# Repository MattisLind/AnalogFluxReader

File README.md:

# AnalogFluxReader
A daughter board to the cheap Cypress  FX2LP demo boards for reading floppy fluxes in analog domain.

This is still very much work in progress. The idea with this project is to read those problematic Memorex 651 disks that I so far has been unsuccessful in reading.

Instead of using the read detector in the drive the idea is to connect the differential signal from the head to this board and then do the all processing in the host PC. 

Please note that some component values, (R and C) in the analog path is just placeholders and is selected in a later stage. The idea that some of them should be easy to change so that filter cut-off frequency and gain can be changed.

The board sits on top of one of those small Cypress FX2LP boards that can be purchased from China cheaply. The FX2LP chip provide a programmable USB interface with high performance. Giving the possibility to sample the A/D converter with up to 48 MSMPS.

## Links
* [The Uncomplicated Universal Usb board](http://lea.hamradio.si/~s57uuu/uuusb/index.htm)
* [adhdengineering](https://adhdengineering.wordpress.com/tag/fx2lp/)
* [Electronics -- USB-FX2 Interface Board (USB-2.0)](https://www.triplespark.net/elec/periph/USB-FX2/)
* [EZ-USB on Linux](http://www.linux-usb.org/ezusb/)
* [Library routines for creating firmware for the Cypress FX2 (CY7C68013 and variants) with SDCC](https://github.com/djmuhlestein/fx2lib)
* [EZ-USB® Technical Reference Manual](https://www.cypress.com/file/126446/download)

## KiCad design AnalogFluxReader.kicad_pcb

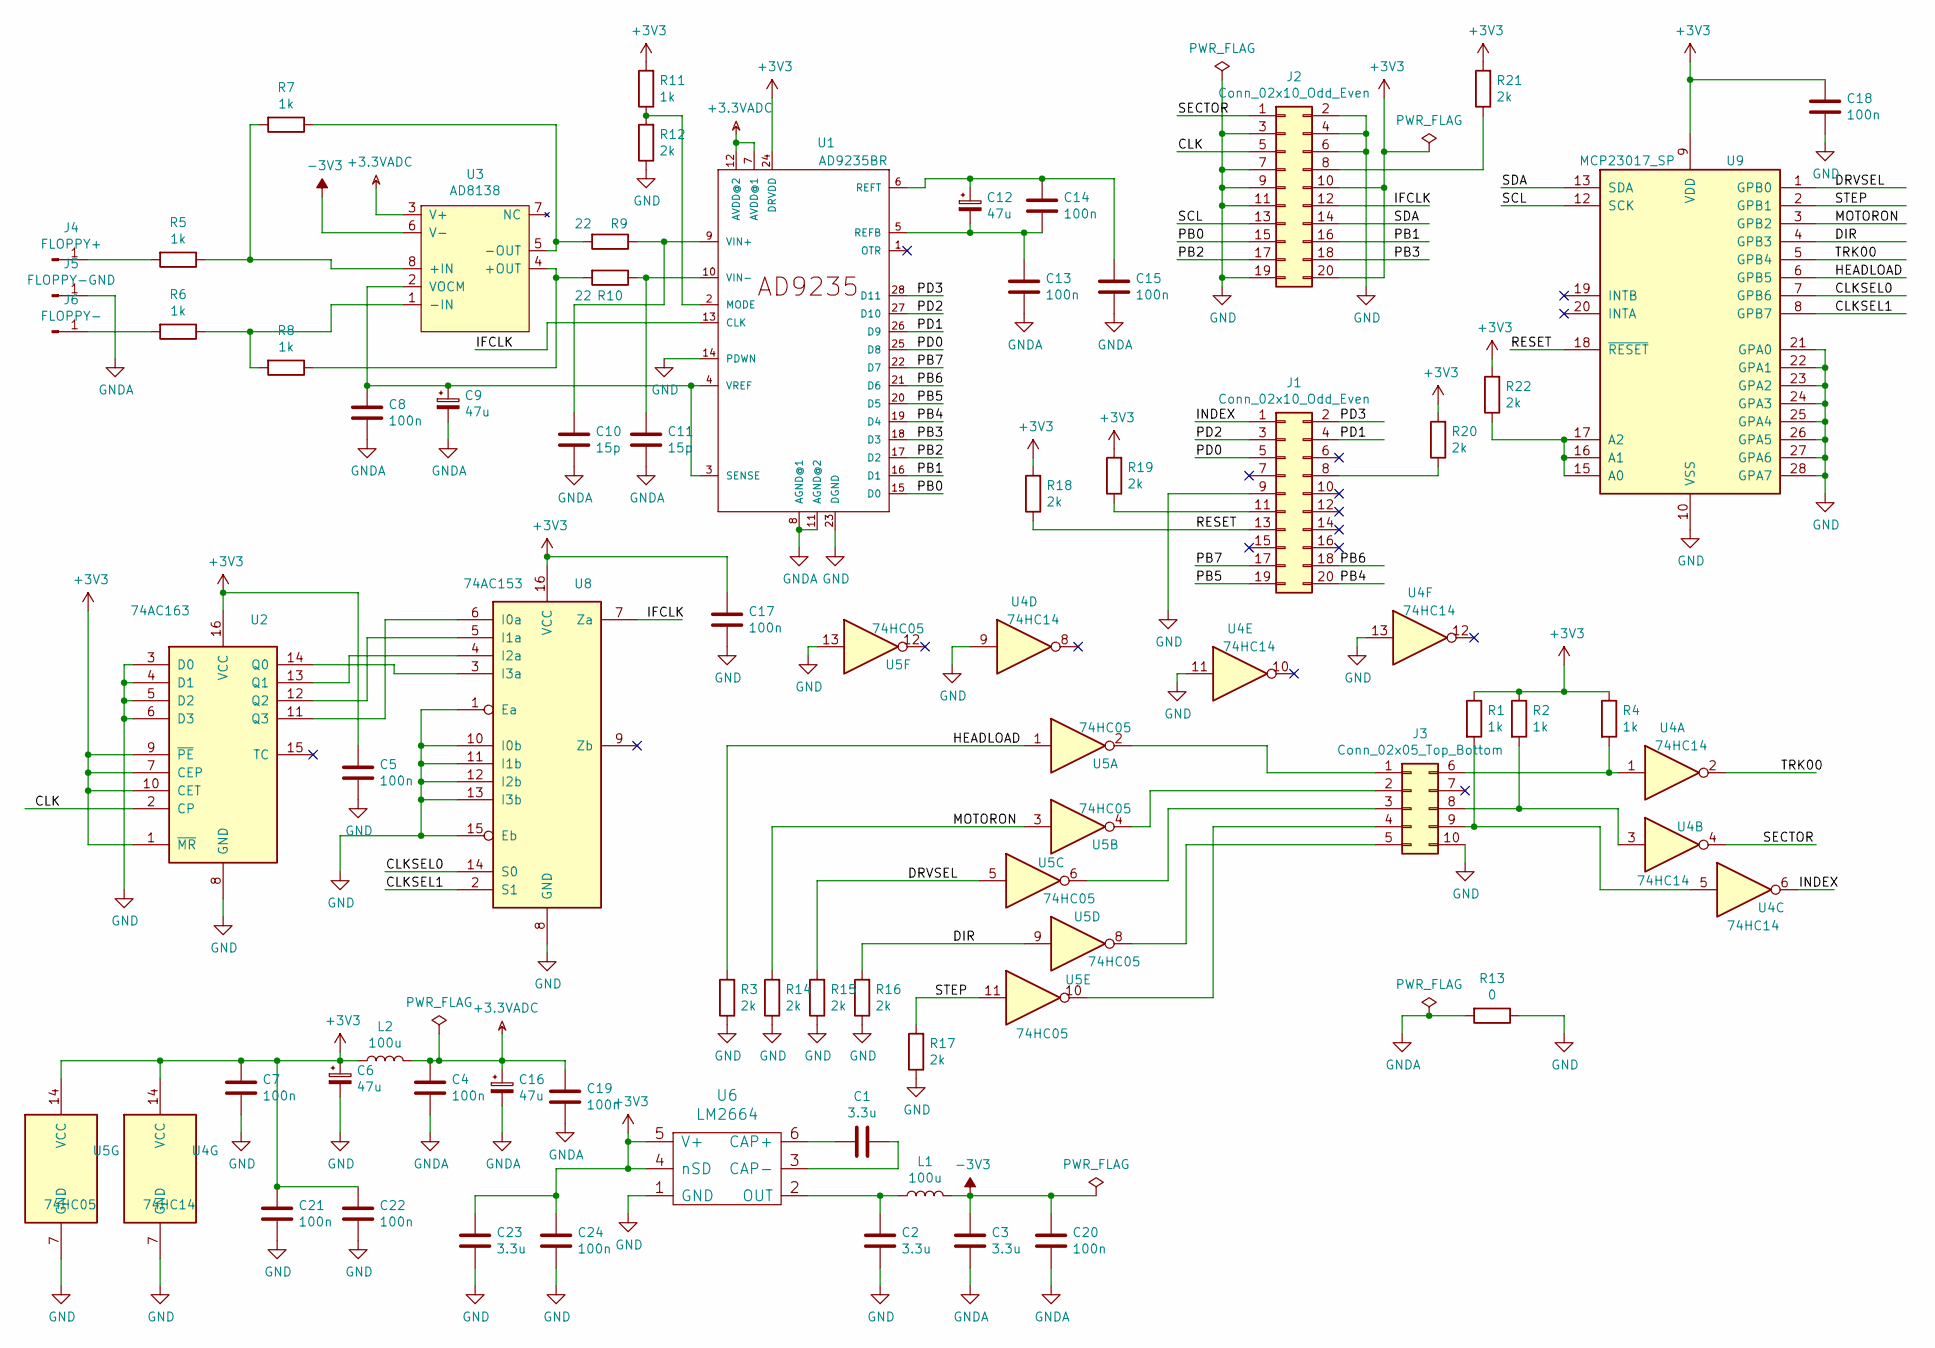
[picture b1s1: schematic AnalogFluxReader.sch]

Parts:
C1, C2, C3, C23: 3.3u; CP_Elec_4x5.4
C4, C5, C7, C8, C13, C14, C15, C17, C18, C19, C20, C21, C22, C24: 100n; C_0805_2012Metric_Pad1.15x1.40mm_HandSolder
C6, C9, C12, C16: 47u; CP_Elec_4x5.4
C10, C11: 15p; C_0805_2012Metric_Pad1.15x1.40mm_HandSolder
J1, J2: Conn_02x10_Odd_Even; PinHeader_2x10_P2.54mm_Vertical
J3: Conn_02x05_Top_Bottom
J4: FLOPPY+; PinHeader_1x01_P2.54mm_Vertical
J5: FLOPPY-GND; PinHeader_1x01_P2.54mm_Vertical
J6: FLOPPY-; PinHeader_1x01_P2.54mm_Vertical
L1, L2: 100u; 1007
R1, R2, R4, R11: 1k; R_0805_2012Metric_Pad1.15x1.40mm_HandSolder
R3, R12, R14, R15, R16, R17, R18, R19, R20, R21, R22: 2k; R_0805_2012Metric_Pad1.15x1.40mm_HandSolder
R5, R6, R7, R8: 1k; R_Axial_DIN0207_L6.3mm_D2.5mm_P7.62mm_Horizontal
R9, R10: 22; R_0805_2012Metric_Pad1.15x1.40mm_HandSolder
R13: 0; R_Axial_DIN0207_L6.3mm_D2.5mm_P7.62mm_Horizontal
U1: AD9235BR; TSSOP-28_4.4x9.7mm_P0.65mm
U2: 74AC163; SOIC-16_3.9x9.9mm_P1.27mm
U3: AD8138; SOIC-8_3.9x4.9mm_P1.27mm; Farnell 2725700
U4: 74HC14; SOIC-14_3.9x8.7mm_P1.27mm
U5: 74HC05; SOIC-14_3.9x8.7mm_P1.27mm
U6: LM2664; SOT-23-6_Handsoldering
U8: 74AC153; SOIC-16_3.9x9.9mm_P1.27mm
U9: MCP23017_SP; SSOP-28_5.3x10.2mm_P0.65mm

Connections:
+3.3VADC: C4.1, C16.1, C19.1, L2.2, U1.7 (AVDD@1), U1.12 (AVDD@2), U3.3 (V+)
+3V3: C5.1, C6.1, C7.1, C17.1, C18.1, C21.1, C22.1, C23.1, C24.1, J2.10, J2.20, L2.1, R1.1, R2.1, R4.1, R11.2, R18.2, R19.2, R20.2, R21.2, R22.2, U1.24 (DRVDD), U2.1 (~MR), U2.7 (CEP), U2.9 (~PE), U2.10 (CET), U2.16 (VCC), U4.14 (VCC), U5.14 (VCC), U6.4 (nSD), U6.5 (V+), U8.16 (VCC), U9.9 (VDD)
-3V3: C3.2, C20.1, L1.2, U3.6 (V-)
/CLK: J2.5, U2.2 (CP)
/CLKSEL0: U8.14 (S0), U9.7 (GPB6)
/CLKSEL1: U8.2 (S1), U9.8 (GPB7)
/DIR: R16.2, U5.9, U9.4 (GPB3)
/DRVSEL: R15.2, U5.5, U9.1 (GPB0)
/HEADLOAD: R3.2, U5.1, U9.6 (GPB5)
/IFCLK: J2.12, U1.13 (CLK), U8.7 (Za)
/INDEX: J1.1, U4.6
/MOTORON: R14.2, U5.3, U9.3 (GPB2)
/PB0: J2.15, U1.15 (D0)
/PB1: J2.16, U1.16 (D1)
/PB2: J2.17, U1.17 (D2)
/PB3: J2.18, U1.18 (D3)
/PB4: J1.20, U1.19 (D4)
/PB5: J1.19, U1.20 (D5)
/PB6: J1.18, U1.21 (D6)
/PB7: J1.17, U1.22 (D7)
/PD0: J1.5, U1.25 (D8)
/PD1: J1.4, U1.26 (D9)
/PD2: J1.3, U1.27 (D10)
/PD3: J1.2, U1.28 (D11)
/RESET: J1.13, R18.1, U9.18 (~RESET~)
/SCL: J2.13, U9.12 (SCK)
/SDA: J2.14, U9.13 (SDA)
/SECTOR: J2.1, U4.4
/STEP: R17.2, U5.11, U9.2 (GPB1)
/TRK00: U4.2, U9.5 (GPB4)
GND: C2.2, C5.2, C6.2, C7.2, C17.2, C18.2, C21.2, C22.2, C23.2, C24.2, J1.9, J2.2, J2.3, J2.4, J2.6, J2.7, J2.9, J2.11, J2.19, J3.10, R3.1, R12.1, R13.1, R14.1, R15.1, R16.1, R17.1, U1.14 (PDWN), U1.23 (DGND), U2.3 (D0), U2.4 (D1), U2.5 (D2), U2.6 (D3), U2.8 (GND), U4.7 (GND), U4.9, U4.11, U4.13, U5.7 (GND), U5.13, U6.1 (GND), U8.1 (Ea), U8.8 (GND), U8.10 (I0b), U8.11 (I1b), U8.12 (I2b), U8.13 (I3b), U8.15 (Eb), U9.10 (VSS), U9.21 (GPA0), U9.22 (GPA1), U9.23 (GPA2), U9.24 (GPA3), U9.25 (GPA4), U9.26 (GPA5), U9.27 (GPA6), U9.28 (GPA7)
GNDA: C3.1, C4.2, C8.1, C9.2, C10.1, C11.1, C13.1, C15.1, C16.2, C19.2, C20.2, J5.1, R13.2, U1.8 (AGND@1), U1.11 (AGND@2)
unnamed: C1.1, U6.3 (CAP-)
unnamed: C1.2, U6.6 (CAP+)
unnamed: C2.1, L1.1, U6.2 (OUT)
unnamed: C8.2, C9.1, U1.3 (SENSE), U1.4 (VREF), U3.2 (VOCM)
unnamed: C10.2, R9.1, U1.9 (VIN+)
unnamed: C11.2, R10.1, U1.10 (VIN-)
unnamed: C12.1, C14.2, C15.2, U1.6 (REFT)
unnamed: C12.2, C13.2, C14.1, U1.5 (REFB)
unnamed: J1.8, R20.1
unnamed: J1.11, R19.1
unnamed: J2.8, R21.1
unnamed: J3.1, U5.2
unnamed: J3.2, U5.4
unnamed: J3.3, U5.6
unnamed: J3.4, U5.10
unnamed: J3.5, U5.8
unnamed: J3.6, R4.2, U4.1
unnamed: J3.8, R2.2, U4.3
unnamed: J3.9, R1.2, U4.5
unnamed: J4.1, R5.2
unnamed: J6.1, R6.2
unnamed: R5.1, R7.2, U3.8 (+IN)
unnamed: R6.1, R8.2, U3.1 (-IN)
unnamed: R7.1, R9.2, U3.5 (-OUT)
unnamed: R8.1, R10.2, U3.4 (+OUT)
unnamed: R11.1, R12.2, U1.2 (MODE)
unnamed: R22.1, U9.15 (A0), U9.16 (A1), U9.17 (A2)
unnamed: U2.11 (Q3), U8.6 (I0a)
unnamed: U2.12 (Q2), U8.5 (I1a)
unnamed: U2.13 (Q1), U8.4 (I2a)
unnamed: U2.14 (Q0), U8.3 (I3a)

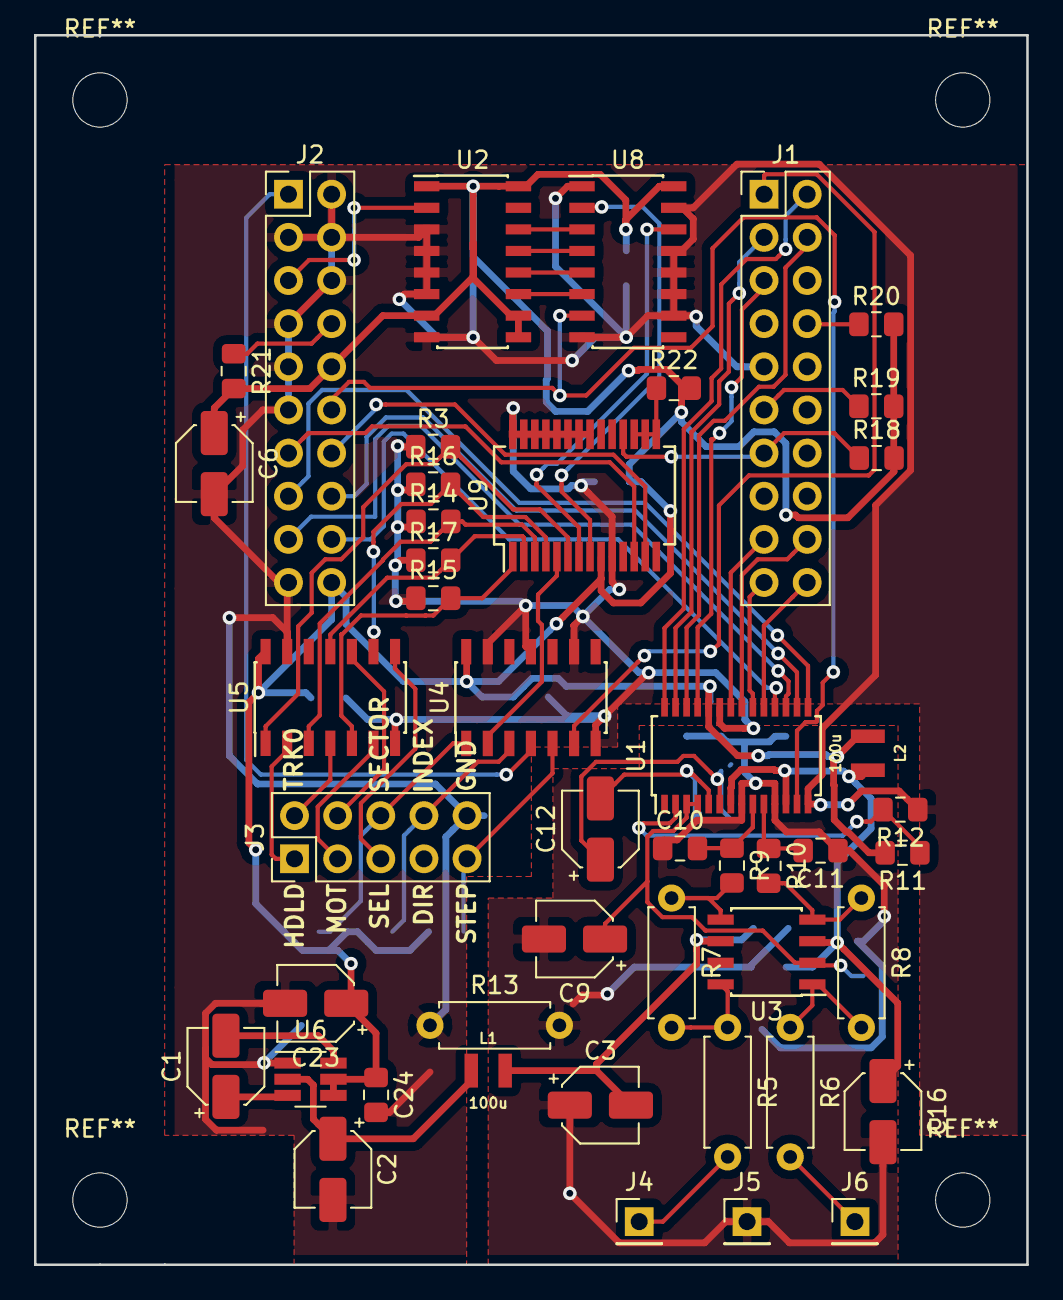
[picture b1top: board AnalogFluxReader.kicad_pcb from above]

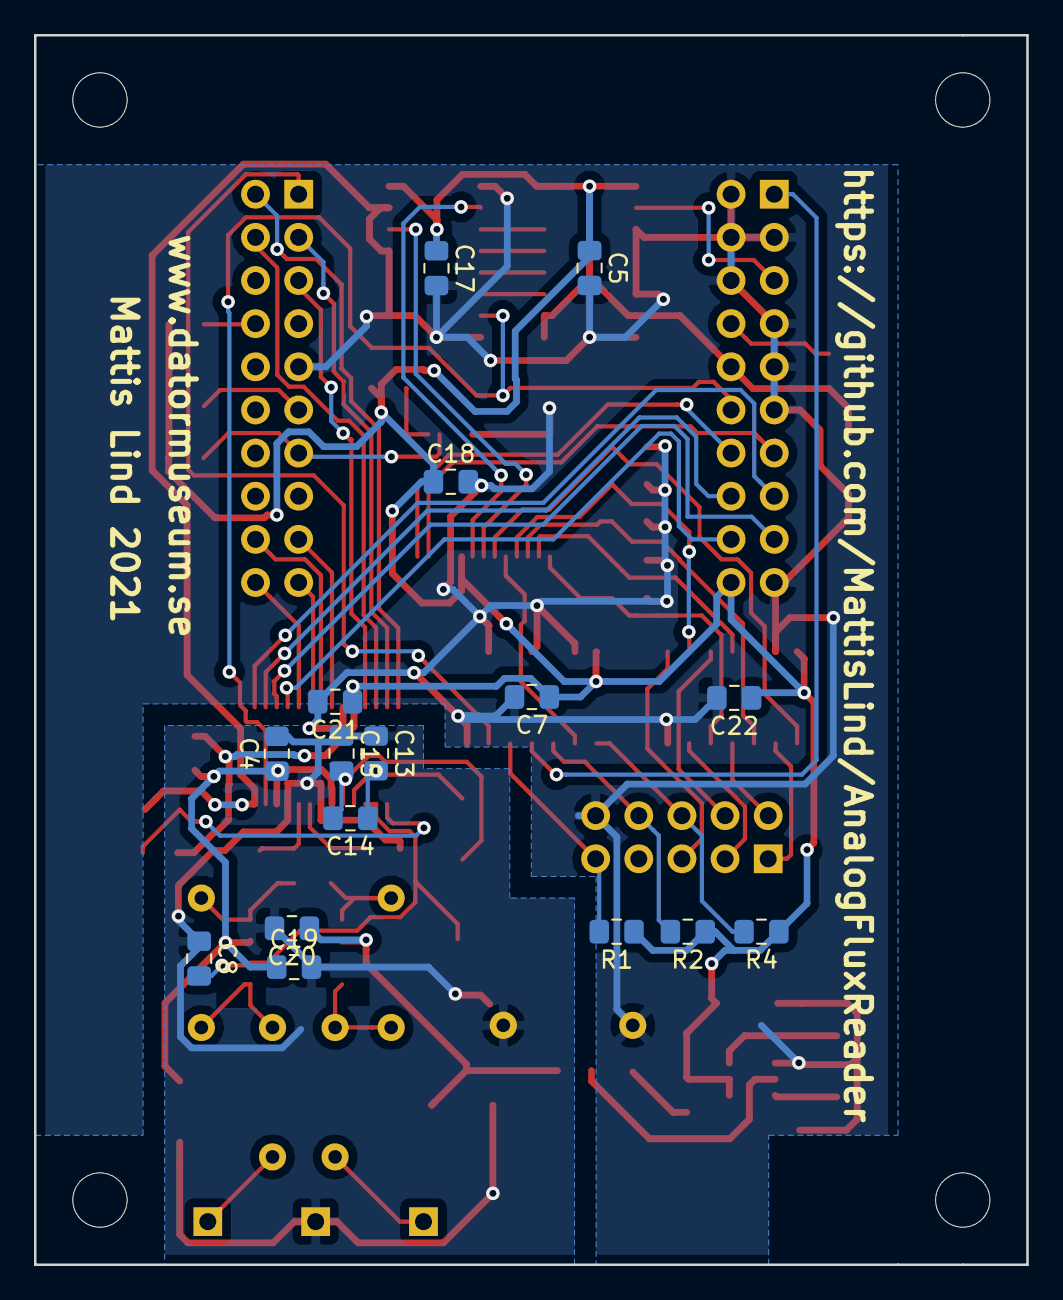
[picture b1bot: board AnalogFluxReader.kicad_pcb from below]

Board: 2 copper layers, 58.4 x 72.4 mm, 62 parts (16 on the bottom side), 63 nets.

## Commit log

2020-06-05 Added files
2020-06-05 Added picture
2020-06-05 Added picture of the fx2lp board.
2020-06-05 Added links
2020-06-05 Spelling
2021-01-14 Updated schematic. Use 74AC163 and 74AC153 instead.
2021-01-15 Update picture.
2021-01-16 Introduced MCP23017 to handle low speed floppy signals. Several PAx pins needed for Slave FIFO.
2021-02-03 Latest pdf converted to png
2021-03-25 Added 1007 layout. Assigned footprints.
2021-03-30 Layout done. Some fixes to schematic.
2021-03-30 Review found some issues.
2021-11-24 Good document for FX2LP development.
